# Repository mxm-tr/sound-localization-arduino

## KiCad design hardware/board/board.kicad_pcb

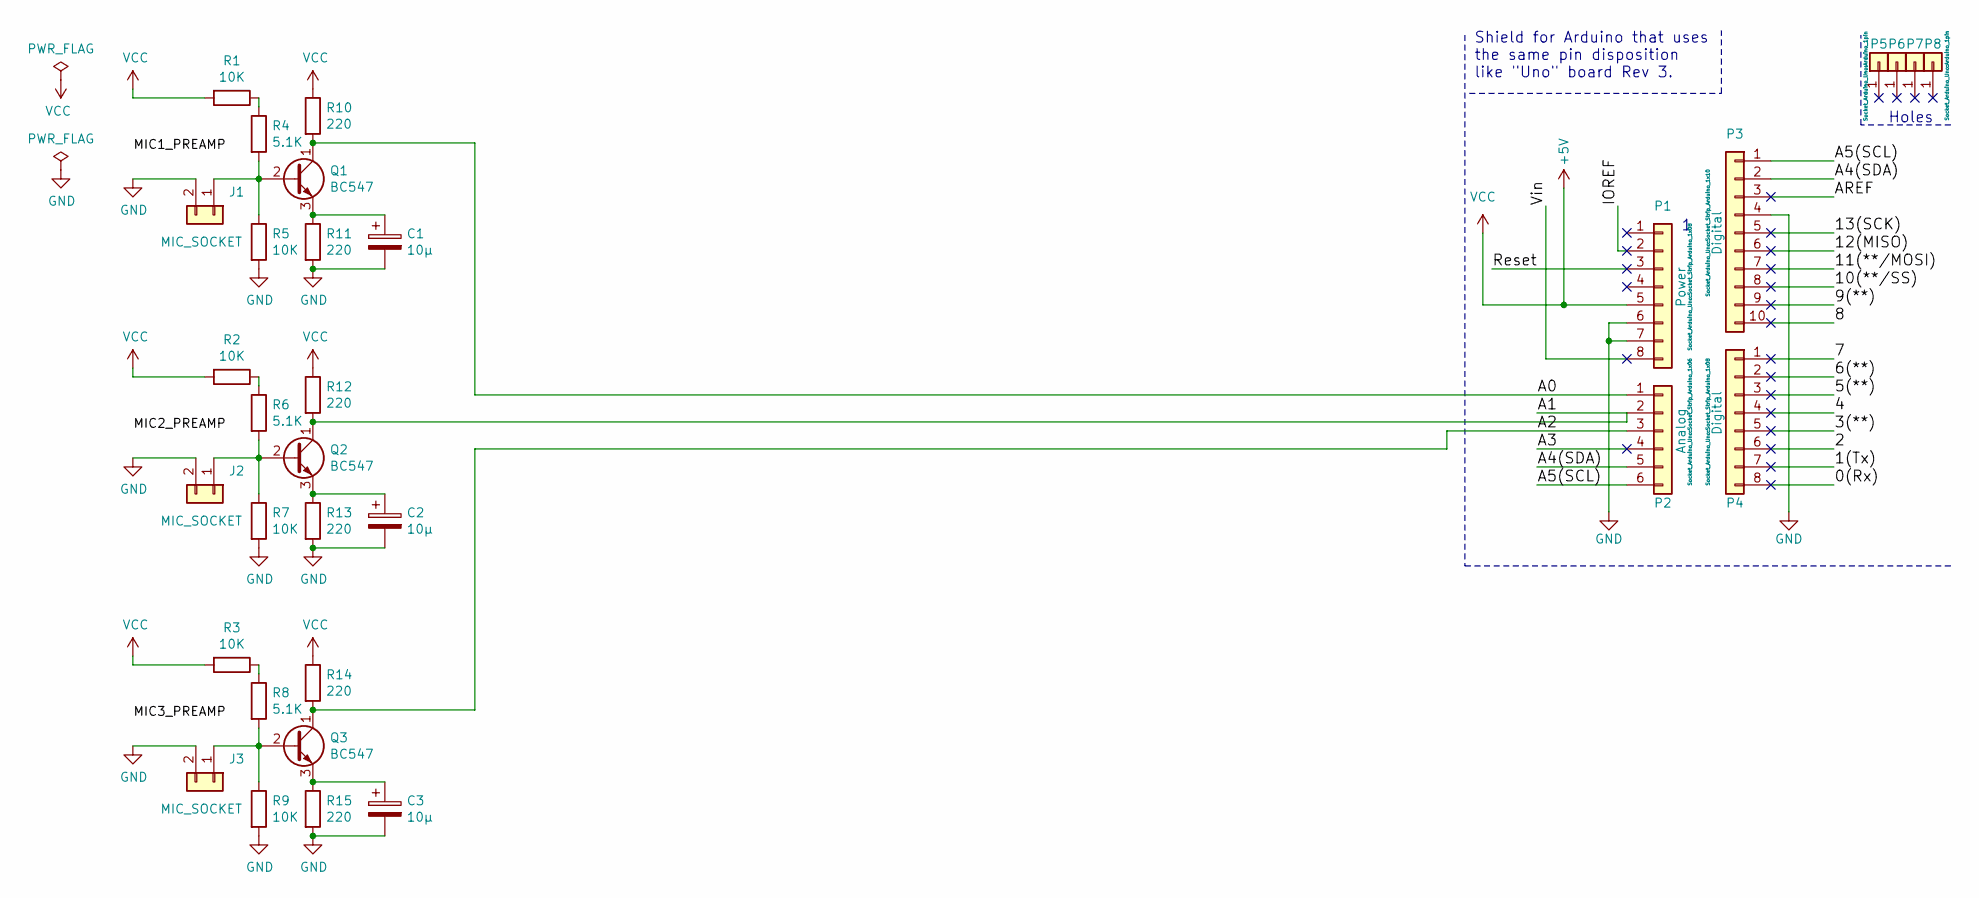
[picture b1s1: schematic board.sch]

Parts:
C1, C2, C3: 10µ; C_Disc_D3.0mm_W1.6mm_P2.50mm
J1, J2, J3: MIC_SOCKET; Pin_D1.0mm_L10.0mm
P1: Power; Socket_Strip_Arduino_1x08
P2: Analog; Socket_Strip_Arduino_1x06
P3: Digital; Socket_Strip_Arduino_1x10
P4: Digital; Socket_Strip_Arduino_1x08
P5, P6, P7, P8: CONN_01X01; Arduino_1pin
Q1, Q2, Q3: BC547; TO-92_Inline
R1, R2, R3, R5, R7, R9: 10K; R_Axial_DIN0204_L3.6mm_D1.6mm_P1.90mm_Vertical
R4, R6, R8: 5.1K; R_Axial_DIN0204_L3.6mm_D1.6mm_P1.90mm_Vertical
R10, R11, R12, R13, R14, R15: 220; R_Axial_DIN0204_L3.6mm_D1.6mm_P1.90mm_Vertical

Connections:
+5V: P1.5, R1.2, R2.2, R3.2, R10.1, R12.1, R14.1
/0(Rx): P4.8
/1(Tx): P4.7
/2: P4.6
/3(**): P4.5
/4: P4.4
/5(**): P4.3
/6(**): P4.2
/7: P4.1
/8: P3.10
/9(**): P3.9
/10(**/SS): P3.8
/11(**/MOSI): P3.7
/12(MISO): P3.6
/13(SCK): P3.5
/A0: P2.1, Q1.1 (C), R10.2
/A1: P2.2, Q2.1 (C), R12.2
/A2: P2.3, Q3.1 (C), R14.2
/A3: P2.4
/A4(SDA): P2.5, P3.2
/A5(SCL): P2.6, P3.1
/AREF: P3.3
/IOREF: P1.2
/Reset: P1.3
/Vin: P1.8
GND: C1.2, C2.2, C3.2, J1.2, J2.2, J3.2, P1.6, P1.7, P3.4, R5.2, R7.2, R9.2, R11.2, R13.2, R15.2
unnamed: C1.1, Q1.3 (E), R11.1
unnamed: C2.1, Q2.3 (E), R13.1
unnamed: C3.1, Q3.3 (E), R15.1
unnamed: J1.1, Q1.2 (B), R4.2, R5.1
unnamed: J2.1, Q2.2 (B), R6.2, R7.1
unnamed: J3.1, Q3.2 (B), R8.2, R9.1
unnamed: R1.1, R4.1
unnamed: R2.1, R6.1
unnamed: R3.1, R8.1

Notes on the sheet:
Holes
Shield for Arduino that uses the same pin disposition like "Uno" board Rev 3.

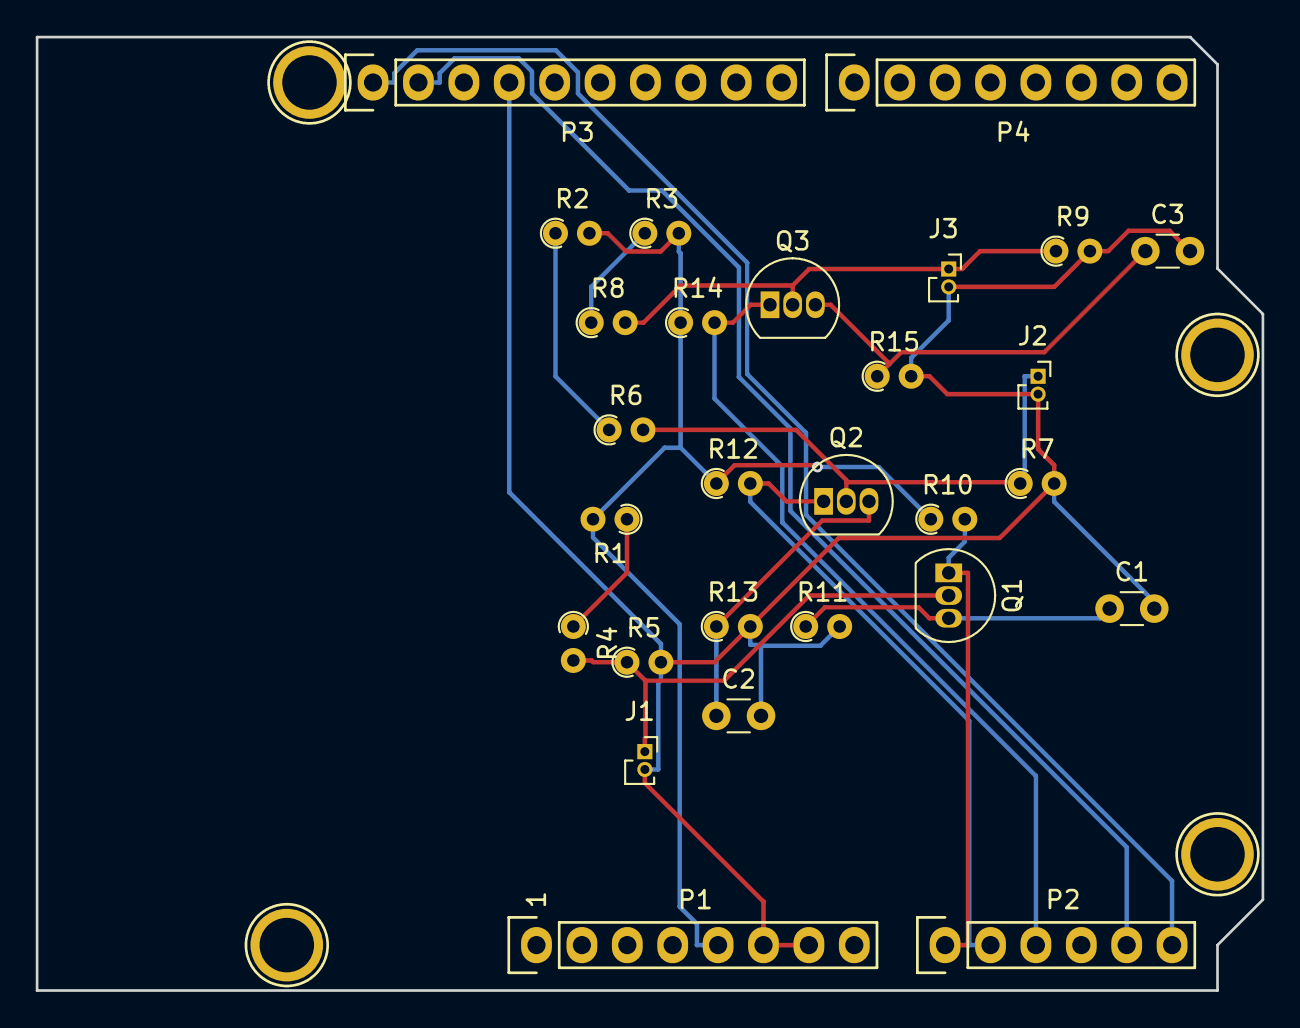
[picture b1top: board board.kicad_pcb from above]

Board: 2 copper layers, 68.6 x 53.3 mm, 32 parts (0 on the bottom side), 16 nets.

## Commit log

2020-11-11 First version of the 3 microphones preamps circuits, not optimized yet
2020-11-21 New microphone inputs sockets
